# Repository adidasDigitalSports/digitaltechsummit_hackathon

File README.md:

# ServiceFactory Smart Jacket Code
#### Arduino program using BLE to communicate with Smartphone App
## Libraries to include:
#### Libraries that need to be copied to "/USER/Documents/Arduino/libraries/"

- **<ArduinoJson.h>** - [https://github.com/bblanchon/ArduinoJson](https://github.com/bblanchon/ArduinoJson) v.5.13.1 (don't use newer version!!!)
- **<FastLED.h>** - IMPORTANT: As of May 2018, the FastLED v.3.1.6 doesn't work with the ESP32, therefore use [https://github.com/samguyer/FastLED](https://github.com/samguyer/FastLED) to compile. v.3.1.6
- **<OneButton.h>** - [https://github.com/mathertel/OneButton](https://github.com/mathertel/OneButton)
 v.1.2.0
- **<OneWire.h>** - [https://github.com/PaulStoffregen/OneWire](https://github.com/PaulStoffregen/OneWire)
 v.2.3.4

#### Libraries that are included within ESP32 Framework - have to exist in "USER/Documents/Arduino/hardware/espressif/esp32/libraries/BLE/" v.0.4.12

- **<BLE2902.h>**
- **<BLEDevice.h>**
- **<BLEServer.h>**
- **<BLEUUID.h>**
- **<BLEUtils.h>**

#### Local header files (contained within the code)

- **"DS2413helper.h"** - local helper file for Touch Inputs from OneWire Chip DS2413  
- **"Ringbuffer.h"** - local helper file for comparing touch inputs ([https://github.com/ankraft/arduino-tools](https://github.com/ankraft/arduino-tools))  
- **"TaskManager.h"** - local helper file for running independently timed tasks ([https://github.com/ankraft/arduino-tools](https://github.com/ankraft/arduino-tools))

# Hardware:
#### Main Controller = Sparkfun ESP32 Thing (Arduino-compatible µC with WiFi/BLE and Battery charging circuit)

- **Pin 19** - Button Input towards GND (Flag button)
- **Pin 22** - WS2811-compatible Neopixel-LEDs (#0-#4 = Intensity, #5-#9 = Progress)
- **Pin 27** - Toggle Power Switch towards GND (Connected to GND = ON, open = OFF)
- **Pin 33** - OneWire Pin connected to DS2413, pulled up 4k7Ω
- **Pin 34** - Battery sensing circuit - Rpup = 1MΩ, Rpdn = 300kΩ Voltage Divider, Rpin = 20kΩ as Input Protection (Pin35 - USB Voltage measure - to be ignored)

#### Touch circuit:

- Communication via One-Wire Protocol - Data Channel is pulled up with a 4k7Ω Resistor
- Protocol Controller Chip: MAXIM DS2413, 2 Port OneWire GPIO Extender
- Touch Chips: Atmel AT42QT1011, QTouch Technology Capacitive Sensing
- Eagle Files for Schematic and PCB are included in [doc/eagle](doc/eagle)

# Inputs:

- Flag Switch:
  - Short Press: Pause/Resume Training, Start Training after Loading from App
  - Long Press: Abort running Training, Restart Training if loaded by App
  - Double Click: Skip running Phase
- Power Switch: (if there is no state change, Power will be ON by default)
  - Closed = Power ON
  - Open   = Power OFF

#### Touch Inputs:
Touch Input can be done on two touch panels, sequentially leading to the following input gestures:

- Short Press Panel A - Vol Down
- Short Press Panel B - Vol Up
- Slide A->B - Volume Up
- Slide B->A - Volume Down        
- Short Press A & B - Play/Pause
- Holding both Panels for >3 seconds - Emergency Call Trigger
- Input Sequences have to be completed between 200 ms and 1,2 sec

#### Config Parameters:

The following settings can be configured in [main.ino](main/main.ino):

- ```int DOTFADE = 64;```  
   0-255 - fading time until running LEDs will turn off. (255 = no fade, 64 = med fade, 1 = very slow fade, 0 = all LEDS stay on)
- ```#define FRAMES_PER_SECOND 43```  
   LED refresh FPS
- ```unsigned long BrightnessTimeout = 4000;```  
  Delay after the LEDs will fade out
- ```int minimalBrightness = 50;```  
  Brightness Percentage to set to after fading out
- ```int MinimumTouchTime = 200;``` 
  Minimum Touch Time to be sensed
- ```int MaximumTouchTime = 1000;```  
  Maximum Touch Time to be sensed
- ```int ICETouchTime = 3000;```
  Delay after which the emergency call will be sent after holding both touch planes
- ```int debounceTouch = 2;```
  values to be removed from start and end of ringbuffer

And in [BLE.ino](main/BLE.ino):

- ```#define DEVICE_NAME "Smarte Jacke"```  
  Bluetooth Broadcasting Name of the Device

#### Compiling / Building:
- install the Arduino IDE (e.g. for Windows [https://www.arduino.cc/download_handler.php?f=/arduino-1.8.5-windows.exe](https://www.arduino.cc/download_handler.php?f=/arduino-1.8.5-windows.exe))
- download all the libraries
- Start Arduino and open Preferences window.
- Enter *https://dl.espressif.com/dl/package_esp32_index.json* into *Additional Board Manager URLs* field. You can add multiple URLs, separating them with commas.
- Open Boards Manager from *Tools > Board* menu and install esp32 platform
  (and don't forget to select your ESP32 board from *Tools > Board* menu after installation).

Alternative, if the above method didn't work for you:

- install the ESP32 Core ([https://learn.sparkfun.com/tutorials/esp32-thing-hookup-guide/installing-the-esp32-arduino-core](https://learn.sparkfun.com/tutorials/esp32-thing-hookup-guide/installing-the-esp32-arduino-core))
- compile and upload using the Arduino IDE
- if necessary, install the FTDI Drivers: [https://learn.sparkfun.com/tutorials/how-to-install-ftdi-drivers/all](https://learn.sparkfun.com/tutorials/how-to-install-ftdi-drivers/all)

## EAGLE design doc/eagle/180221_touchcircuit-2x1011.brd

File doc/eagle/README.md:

# ServiceFactory Smart Jacket Touch Circuit
#### PCB for Touch Sensing from two Inputs, sending both signals over the OneWire-Bus
###### Components used:
-  2x AT42QT1011   - Capacitive Touch Chip
-  1x DS2413       - OneWire Converter
- 2x Cf 100nF
- 2x Cs 68nF
- 2x Cx 5.6pF
- 2x R0 0Ω
- 1x Rp 4.7kΩ
- 2x Rs 220Ω

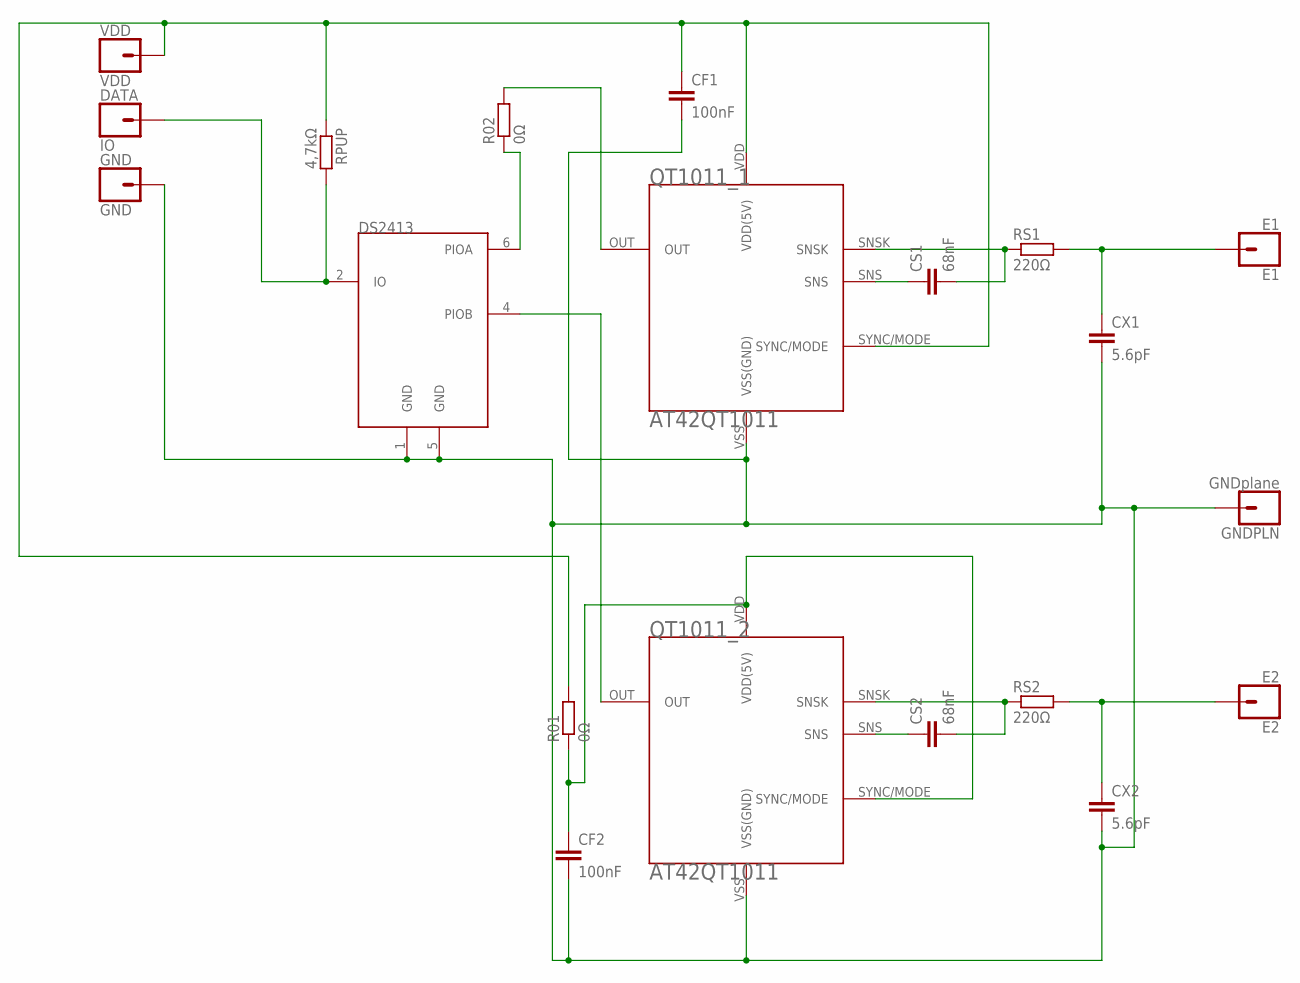
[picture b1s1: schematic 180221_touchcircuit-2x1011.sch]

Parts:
CF1, CF2: 100nF; C1206
CS1, CS2: 68nF; C1206
CX1, CX2: 5.6pF; C1206
DATA: IO; 1X01
DS2413: DS2413(TSOC6); TSOC6
E1: E1; 1X01
E2: E2; 1X01
GND: GND; 1X01
GNDPLN: GNDplane; 1X01
QT1011_1, QT1011_2: AT42QT1011
R01, R02: 0Ω; R1206
RPUP: 4,7kΩ; R1206
RS1, RS2: 220Ω; R1206
VDD: VDD; 1X01

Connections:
E1: CX1.1, E1.1, RS1.2
E2: CX2.1, E2.1, RS2.2
GND: CF1.2, CF2.2, CX1.2, CX2.2, DS2413.1 (GND), DS2413.5 (GND), GND.1, GNDPLN.1, QT1011_1.VSS (VSS(GND)), QT1011_2.VSS (VSS(GND))
unnamed: CS1.1, QT1011_1.SNS
unnamed: DS2413.4 (PIOB), QT1011_2.OUT
unnamed: DS2413.6 (PIOA), R02.1
unnamed: QT1011_1.OUT, R02.2
unnamed: CS2.2, QT1011_2.SNSK, RS2.1
unnamed: CS2.1, QT1011_2.SNS
unnamed: DATA.1, DS2413.2 (IO), RPUP.2
SNSK1: CS1.2, QT1011_1.SNSK, RS1.1
VDD: CF1.1, QT1011_1.SYNC/MODE, QT1011_1.VDD (VDD(5V)), R01.2, RPUP.1, VDD.1
VDD-R0: CF2.1, QT1011_2.SYNC/MODE, QT1011_2.VDD (VDD(5V)), R01.1

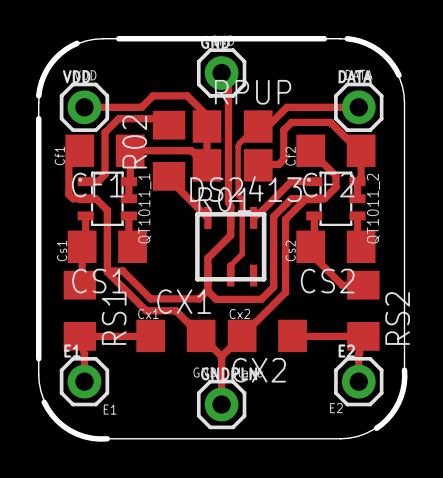
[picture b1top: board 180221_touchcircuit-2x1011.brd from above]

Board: 2 copper layers, 20.3 x 22.2 mm, 20 parts (0 on the bottom side), 13 nets.

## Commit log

2018-10-18 Code for digital tech summit hackathon.

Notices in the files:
doc/eagle/180221_touchcircuit-2x1011.brd:
© Christian Pflug
parts and their libraries:
SparkFun-Connectors: Licensing: Creative Commons ShareAlike 4.0 International - https://creativecommons.org/licenses/by-sa/4.0
